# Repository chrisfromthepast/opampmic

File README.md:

# opampmic
super simple phantom powered electret impedance converter and doug self style balanced output. As discrete JFETS are harder to come by, this circuit takes advantage of the FETS inside of a popular Op amp.

This PCB was designed to fit inside Zramo 104, and with the stock capsule, it sounds 1000 times better than the original mic. This PCB will also fit inside of MXL 603s type bodies. 

circuit designed by Jules Ryckebusch, PCB layout by me Chris Williams. I first saw this circuit here:https://www.instructables.com/OPA-Based-Alice-Microphones-a-Cardioid-and-a-Figur/

Jules has an alternate design that is impedance balanced, which is also worth a shot, as well as a version for true condensers.

I have been really happy with this little circuit.

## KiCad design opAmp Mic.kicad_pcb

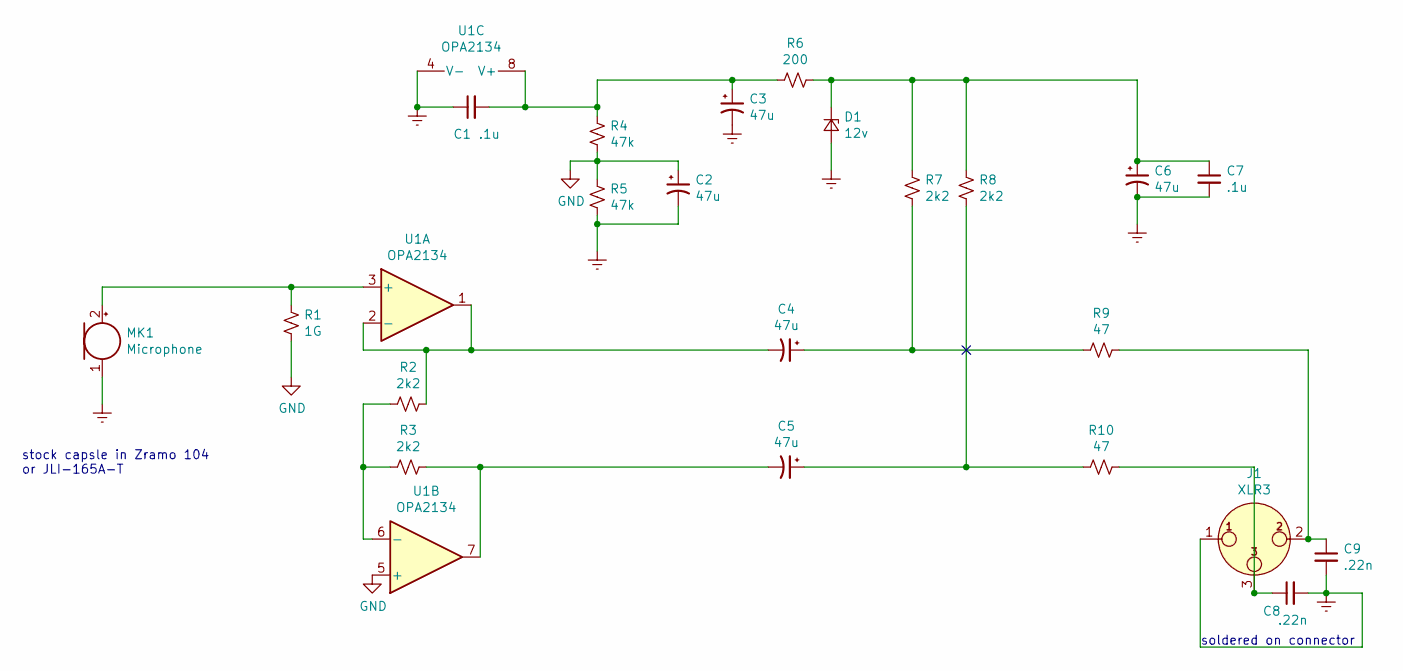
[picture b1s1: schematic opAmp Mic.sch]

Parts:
C1, C7: .1u; C_Disc_D3.0mm_W2.0mm_P2.50mm
C2, C4, C5, C6: 47u; CP_Radial_D6.3mm_P2.50mm
C3: 47u; CP_Radial_D4.0mm_P1.50mm
C8, C9: .22n; C_Disc_D3.0mm_W1.6mm_P2.50mm
D1: 12v; Diode_DO-35_P10mm
J1: XLR3; SolderWirePad_3x_0-8mmDrill
MK1: Microphone; PinHeader_1x2_P2.54mm_Drill1.02mm
R1: 1G; R_Axial_DIN0309_L9.0mm_D3.2mm_P25.40mm_Horizontal
R2, R3, R7, R8: 2k2; R_Axial_DIN0204_L3.6mm_D1.6mm_P2.54mm_Vertical
R4, R5: 47k; R_Axial_DIN0204_L3.6mm_D1.6mm_P2.54mm_Vertical
R6: 200; R_Axial_DIN0204_L3.6mm_D1.6mm_P2.54mm_Vertical
R9, R10: 47; R_Axial_DIN0204_L3.6mm_D1.6mm_P2.54mm_Vertical
U1: OPA2134; DIP-8_W7.62mm

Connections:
Earth: C1.1, C2.2, C3.2, C6.2, C7.2, C8.2, C9.2, D1.2 (A), J1.1, MK1.1 (-), R5.2, U1.4 (V-); also elsewhere on the board
GND: C2.1, R1.2, R4.2, R5.1, U1.5 (+); also elsewhere on the board
unnamed 2: C1.2, C3.1, R4.1, R6.2, U1.8 (V+); also elsewhere on the board
unnamed: C4.1, R7.2, R9.2
unnamed 4: C4.2, R2.1, U1.1, U1.2 (-); also elsewhere on the board
unnamed: C5.1, R8.2, R10.2
unnamed 6: C5.2, R3.1, U1.7; also elsewhere on the board
unnamed: C6.1, C7.1, D1.1 (K), R6.1, R7.1, R8.1
unnamed: C8.1, J1.3, R10.1
unnamed: C9.1, J1.2, R9.1
unnamed 10: MK1.2 (+), R1.1, U1.3 (+); also elsewhere on the board
unnamed 11: R2.2, R3.2, U1.6 (-); also elsewhere on the board

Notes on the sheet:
soldered on connector
stock capsle in Zramo 104 or JLI-165A-T

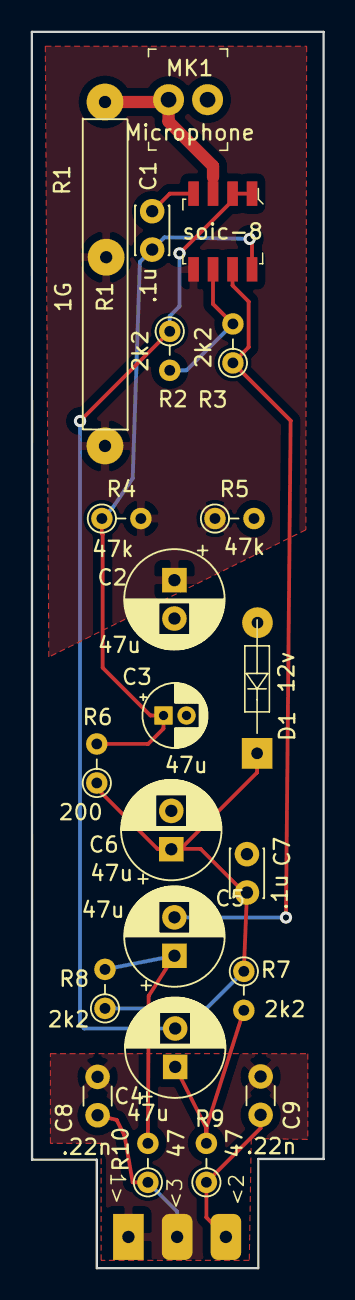
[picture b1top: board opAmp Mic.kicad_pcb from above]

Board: 2 copper layers, 19.0 x 80.5 mm, 23 parts (0 on the bottom side), 12 nets.

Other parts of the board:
soic-8: SOIC-8_W5.3mm

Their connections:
Earth: soic-8.4; also elsewhere on the board
GND: soic-8.5; also elsewhere on the board
unnamed 2: soic-8.8; also elsewhere on the board
unnamed 4: soic-8.1, soic-8.2; also elsewhere on the board
unnamed 6: soic-8.7; also elsewhere on the board
unnamed 10: soic-8.3; also elsewhere on the board
unnamed 11: soic-8.6; also elsewhere on the board

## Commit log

2021-05-08 initial jlc pcb run with 2 serious errors
2021-05-08 added notes describing what was wrong with the original order from JLC PCB with 2 bodes, I got it working, but there are some issues with part placement that also need fixing
2021-05-08 lined up capacitors in the center line remade nets after moving everything
2021-05-14 ready for release and board spin
2021-05-14 cleaned up 1 trace for only aesthetic reasons
2021-05-15 fixed some issues raised by DRC, moved some labels around
2021-05-15 getting ready for an official release
2021-06-02 exported gerbers with updated shape and placement corrections to do: turn smt around to make high impedance path shorter
2021-06-02 moved op amp, changed current paths , enlarged and shortened high impedence nets
2021-06-11 small changes to layout, don't recall exactly
2021-07-19 made the capsule ground sit on the chassis rather than the virtual ground, which solves some of the issues I had with the initial pcb run
2021-07-20 cleaned up some text in the schematic
2021-10-13 changed a few screenprints, and modified the xlr connector 1st commit using different command line on different computer, lets see how it works
